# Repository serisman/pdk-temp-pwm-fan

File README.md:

# pdk-temp-pwm-fan
A temperature controlled PWM fan controller using an inexpensive (3 cent) 8-bit Padauk microcontroller.

### Links
- [Firmware](firmware/)
- [PCB](pcb-u06/)

This fan controller drives a common 4-pin PC fan, by sending a 25 kHz PWM signal with a varying duty cycle.
The duty cycle is adjusted up or down based on a high and low temperature set point.
- If the temperature is below the low set point, the PWM duty is decreased by 1 every 1/3 second until it the fan is off (or as slow as it can go).
- If the temperature is above the high set point, the PWM duty cycle is increased by 1 times the number increments above the high set point every 1/3 second until the fan is fully on.

The temperature is measured using a 10K NTC thermistor between VCC and a 1K resistor to GND forming a voltage divider.
- The output of this voltage divider is fed into the Padauk microcontroller's Comparator + input.
- The Comparator's - input is connected to an internally generated voltage source that can be set to 16 different voltage levels between GND and 1/2 VCC.
- So, by changing the internal voltage source, the Comparator can be checked to see if the NTC's output is greater or less than a set point.

This temperature measurement isn't particularly precise, but should suffice for crude temperature control requirements,
like cooling down a heatsink in a power supply or UPS, with minimal power loss and noise when cooling isn't required.

### Schematic
> 

### Compatibility
This project is currently intended to be run on the PMS150C Padauk microcontrollers,
but it should be able to be run on pretty much any other Padauk microcontrollers that have a Comparator (most)
and that are supported by SDCC and the Easy PDK Programmer.

### Images

### Copyright and License:
- Copyright (C) 2020 - serisman (github@serisman.com)
- License: [GPL v3 (or later)](LICENSE)

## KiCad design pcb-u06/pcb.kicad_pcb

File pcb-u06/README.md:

# pcb-u06 (pdk-temp-pwm-fan)

### Schematic
> 

### PCB

This PCB design was created with KiCad, and has been [shared on OSHPARK](https://oshpark.com/shared_projects/2kFmPXyn).
There are also gerber files available in the [output/gerber/](output/gerber/) directory.

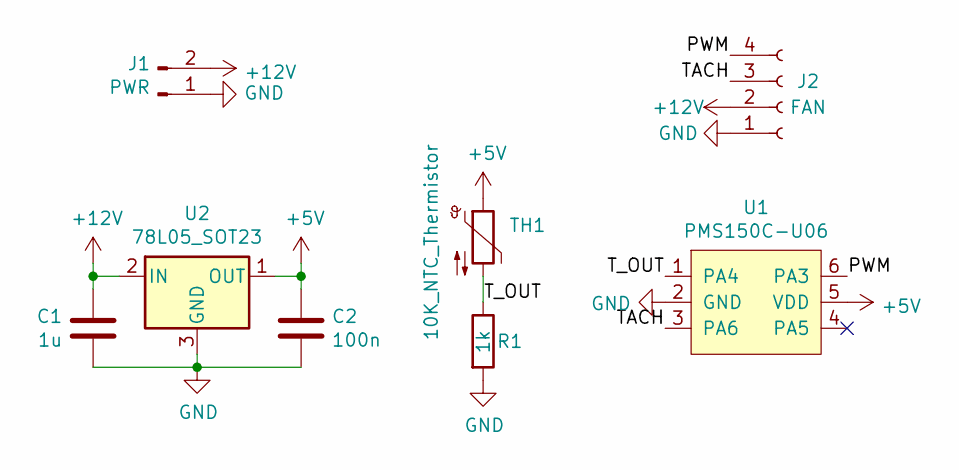
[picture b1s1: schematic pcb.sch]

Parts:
C1: 1u; C_0805
C2: 100n; C_0805
J1: PWR; PinSocket_1x02_P2.54mm_Vertical
J2: FAN; PinSocket_1x04_P2.54mm_Vertical
R1: 1k; R_0805
TH1: 10K_NTC_Thermistor; PinSocket_1x02_P2.54mm_Vertical
U1: PMS150C-U06; SOT-23-6
U2: 78L05_SOT23; SOT-23

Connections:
+5V: C2.1, TH1.1, U1.5 (VDD), U2.1 (OUT)
+12V: C1.2, J1.2, J2.2, U2.2 (IN)
/PWM: J2.4, U1.6 (PA3)
/TACH: J2.3, U1.3 (PA6)
/T_OUT: R1.1, TH1.2, U1.1 (PA4)
GND: C1.1, C2.2, J1.1, J2.1, R1.2, U1.2 (GND), U2.3 (GND)

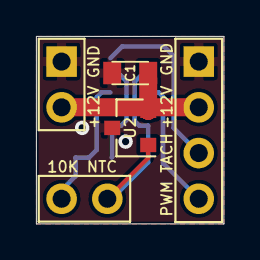
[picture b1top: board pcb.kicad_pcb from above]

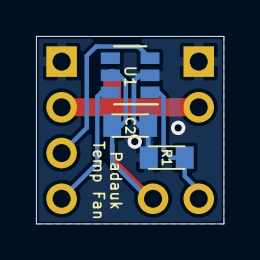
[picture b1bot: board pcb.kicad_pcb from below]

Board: 2 copper layers, 10.4 x 10.4 mm, 8 parts (3 on the bottom side), 6 nets.

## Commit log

2020-10-06 Initial Version
2020-10-06 Fix some links
2020-10-06 Add supporting docs
2020-10-06 fix typo
2020-10-06 typo
2026-06-06 Update to support newer versions of SDCC
